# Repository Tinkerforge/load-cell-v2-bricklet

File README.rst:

Load Cell Bricklet 2.0
======================

This repository contains the firmware source code and the hardware design
files. The documentation generator configs can be found at
https://github.com/Tinkerforge/generators

Repository Content
------------------

software/:
 * examples/: Examples for all supported languages
 * build/: Compiled files
 * src/: Source code of firmware
 * Makefile: Makefile to build project

hardware/:
 * Contains KiCad project files and additionally schematics as PDF

datasheets/:
 * Contains datasheets for sensors and complex ICs that are used

Hardware
--------

The hardware is designed with the open source EDA Suite KiCad
(http://www.kicad.org). Before you are able to open the files,
you have to install the Tinkerforge kicad-libraries
(https://github.com/Tinkerforge/kicad-libraries). You can either clone
them directly in hardware/ or clone them in a separate folder and
symlink them into hardware/
(ln -s kicad_path/kicad-libraries project_path/hardware). After that you
can open the .pro file in hardware/ with KiCad and from there view and
modify the schematics and the PCB layout.

Software
--------

If you want to do your own Brick/Bricklet firmware development we highly
recommend that you use our build environment setup script and read the
tutorial (https://www.tinkerforge.com/en/doc/Tutorials/Tutorial_Build_Environment/Tutorial.html).

To compile the C code we recommend you to install the newest GNU Arm Embedded
Toolchain (https://launchpad.net/gcc-arm-embedded/+download).
You also need to install bricklib2 (https://github.com/Tinkerforge/bricklib2).

You can either clone it directly in software/src/ or clone it in a
separate folder and symlink it into software/src/
(ln -s bricklib_path/bricklib2 project_path/software/src/). Finally make sure to
have CMake installed (http://www.cmake.org/cmake/resources/software.html).

After that you can build the firmware by invoking make in software/.
The firmware (.zbin) can then be found in software/build/ and uploaded
with brickv (click button "Flashing" on start screen).

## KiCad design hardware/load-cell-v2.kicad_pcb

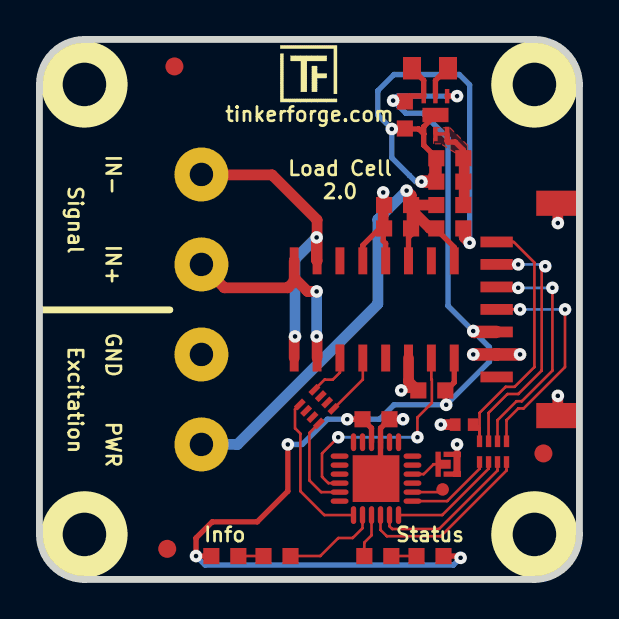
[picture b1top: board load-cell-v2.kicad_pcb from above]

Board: 2 copper layers, 30.0 x 30.0 mm, 33 parts (1 on the bottom side), 26 nets.

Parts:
C1: 220pF; C0402F
C2, C5, C6, C7, C8: 100nF; C0603F
C3: 2.2µF; C0603F
C4: 4.7µF; C0603F
C9: 1µF; C0603F
D1: green; D0603F
D2: blue; D0603F
Fiducial_Mark: VAL**; Fiducial_Mark
Fiducial_Mark#2, Fiducial_Mark#3: VAL**; Fiducial_Mark
L1: 1µH; C0805
L2: FB0603-2; R0603F
P1: CON-SENSOR; CON-SENSOR2
P2: Boot; SolderJumper
P3: Debug; DEBUG_PAD
P4, P5: AKL_5_2
R1, R2: 1k; R0603F
RP1, RP2: 82; 4X0402
U1: XMC1100; QFN24-4x4mm-0.5mm
U2: FAN4860; UMLP_22
U3: HX711; SOP16L
U4, U5, U6, U7: DRILL; DRILL_NP
VAL: CE_5mm

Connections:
3V3: C2.1, C3.2, C7.2, D1.1, D2.1, L1.1, P1.3, U1.10, U2.4, U2.6, U3.16
+5V: C4.2, C5.1, L2.2, U2.2, U2.3
+5VA: C6.2, C8.1, C9.1, L2.1, P5.1, U3.1, U3.3
AGND: C1.2, C2.2, C3.1, C4.1, C5.2, C6.1, C7.1, C8.2, C9.2, P1.2, P1.EP, P2.1, P5.2, U1.9, U1.EXP, U2.1, U2.EP, U3.4, U3.5, U3.14
DOUT: RP2.8, U1.17
unnamed: C1.1, P1.7, RP1.4
unnamed: D1.2, R1.2
unnamed: D2.2, R2.2
unnamed: L1.2, U2.5
unnamed: P1.4, RP1.1
unnamed: P1.5, RP1.2
unnamed: P1.6, RP1.3
unnamed: P2.2, U1.4
unnamed: P3.1, U1.2
unnamed: P4.1, U3.8, U3.10
unnamed: P4.2, U3.7, U3.9
unnamed: R1.1, U1.20
unnamed: R2.1, U1.21
unnamed: RP2.1, U3.12
unnamed: RP2.4, U3.11
PD_SCK: RP2.5, U1.19
RATE: U1.16, U3.15
S-CLK: RP1.7, U1.23
S-CS: RP1.8, U1.22
S-MISO: RP1.5, U1.1
S-MOSI: RP1.6, U1.24

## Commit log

2018-01-11 add hardware files for new prototype
2018-01-11 add readme file
2018-01-15 change via defaults
2018-02-15 Add datasheet
2018-02-15 Add gitignore
2018-02-15 Add initial stub implementation of software and API
2018-02-15 change "Status" and "LED" led colors
2018-02-20 Cleanup KiCad libraries config
    Ensure LibDir=kicad-libraries and LibName1=tinkerforge.
    Remove special library.
2018-03-05 Remove unused flash-size define
2018-03-15 drc check
2018-03-16 rename LED
2018-03-16 Add hx711 readout and API implementation
2018-03-26 Implement info LED support
2018-03-27 specify processor
2018-03-28 Fix initial info LED config
2018-03-28 Return invalid parameter
2018-03-28 Fix info LED config implementation
2018-03-28 Fix info LEd API naming
2018-04-16 Add 3d information (final)
2018-04-16 Add 3d model (*.FCStd & *.step)
2018-05-04 Rename files
2018-05-04 Add schematic PDF
2018-05-25 Add examples
2018-05-30 Allow negative calibration
2018-06-04 Disable debug
2018-06-06 Adapt to bricklib2 callback-value changes to fix wrong threshold min/max type
2018-06-07 Update changelog for initial release
2018-06-18 Change capacitor footprint(s) to C0402F
2018-06-28 Fix readme
2018-07-11 Add Makefile with docker support
2018-07-11 Update directory structure and build instructions
2018-07-11 Remove obsolete generate_makefile scripts
2018-10-04 Increase version for new release (changes in bricklib2)
2018-10-04 Add rev to changelog
2018-11-07 rust: Accept host names for ip connection, fix naming inconsistencies
2018-11-07 rust: Rename callback receivers.
2018-12-14 Add go examples.
2018-12-18 go: Change import path.
2018-12-18 go: Change import path again.
2018-12-20 rust: Reformat examples.
2019-01-24 mqtt: Add examples.
2019-01-24 mqtt: Fix example header.
2019-01-24 mqtt: Remove executable bit in example permissions.
2019-01-24 go: Minor example fixes.
2019-01-24 mqtt: Minor example fixes.
2019-03-28 mqtt: Fix whitespace.
2019-08-22 c: Adapt to bindings changes
2020-01-13 examples: Use python3 input instead of python2 raw_input.
2020-01-13 examples: mqtt: Remove trailing whitespace.
2020-08-19 Add uc examples.
2020-08-25 uc: Fix whitespace
2020-08-27 uc: Fix warnings.
2020-08-31 uc: Use fixed-with placeholders in format strings.
2020-09-02 uc: Add example driver note.
2021-10-25 Update KiCad link
    https://www.kicad.org/blog/2021/10/Avoid-links-to-former-kicad-domain/
2022-04-19 examples: uc: Rename TF_HalContext to TF_HAL.
2022-04-27 uc: Adapt to bindings changes
2022-05-10 go: Fix format string
2022-07-06 Add license files.
2023-06-21 move to new kicad version

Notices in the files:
hardware/load-cell-v2.kicad_pcb:
Licensed under CERN OHL v.1.1
Copyright (©) 2018, B.Nordmeyer
Copyright Tinkerforge GmbH 2018.
This documentation describes Open Hardware and is licensed under the
CERN OHL v. 1.1.
